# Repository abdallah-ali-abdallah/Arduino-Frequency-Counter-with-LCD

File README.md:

Arduino-Frequency-Counter-with-LCD
==================================

Arduino Frequency Counter with LCD, Everything is Embedded in a single Layer PCB
with maximum frequency input up-to 64 Mhz

  Arduino Frequency Counter (up to 64 Mhz) with LCD
  
  By: Abdallah Ali Abdallah
  
  Date: Aug-2014
  
  Licence: CC-BY-NC V.4
  
  E-mail: abdallah.ali.abdallah.elmasry@gmail.com

  Note: This counter is based on chip 74xx93 (counter) used as a frequency divider by 8
  the maximum bandwidth for arduino to count is 8 Mhz and we can multiply this number 
  using 74xx93 or any other counter chip.

  the new bandwidth is determined by the counter maximum clock rate
  for example: 

  chip 74-LS-93 has (Max clock = 42 Mhz) - so you can measure up to 42 Mhz
  
  chip 74-HC-93 has (Max clock = 64 Mhz) - so you can measure up to 64 Mhz
  
  Note: Minmum input voltage is 2 volt
		    Maximum input voltage is 5.1 volt
		
=============================================	

  This project Based on counter Library by:  
  
  Martin Nawrath KHM LAB3
  Kunsthochschule f¸r Medien Kˆln
  Academy of Media Arts
  http://www.khm.de
  http://interface.khm.de/index.php/labor/experimente/

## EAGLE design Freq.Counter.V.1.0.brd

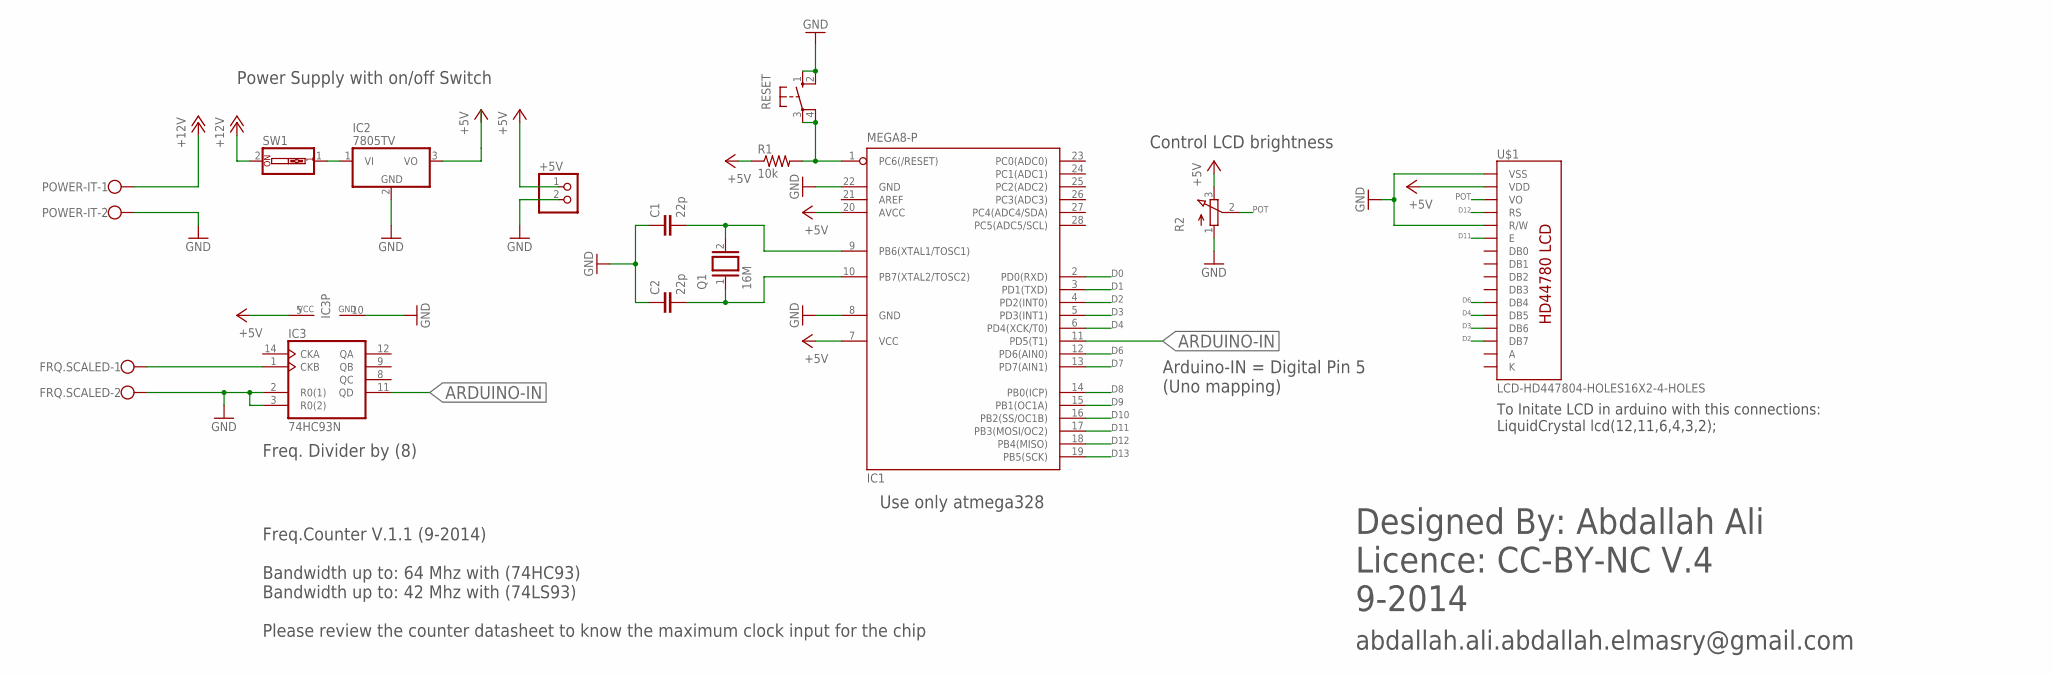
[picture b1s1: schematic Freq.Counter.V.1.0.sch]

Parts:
+5V: PINHD-1X2; 1X02
C1, C2: 22p; C025-025X050
FRQ.SCALED: W237-102
IC1: MEGA8-P; DIL28-3
IC2: 7805TV; TO220V
IC3: 74HC93N; DIL14
POWER-IT: W237-102
Q1: 16M; QS
R1: 10k; 0207/10
R2: 3RP/1610N
RESET: 10-XX; B3F-10XX
SW1: SW_DIP-1; EDG-01
U$1: LCD-HD447804-HOLES16X2-4-HOLES; LCD-16X2-4HOLES

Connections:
+5V: +5V.1, IC1.7 (VCC), IC1.20 (AVCC), IC2.3 (VO), IC3.5 (VCC), R1.1, R2.3 (E), U$1.2 (VDD)
+12V: POWER-IT.1, SW1.2
A: U$1.15 (A)
ARDUINO-IN: IC1.11 (PD5(T1)), IC3.11 (QD)
D0: IC1.2 (PD0(RXD))
D1: IC1.3 (PD1(TXD))
D2: IC1.4 (PD2(INT0)), U$1.14 (DB7)
D3: IC1.5 (PD3(INT1)), U$1.13 (DB6)
D4: IC1.6 (PD4(XCK/T0)), U$1.12 (DB5)
D6: IC1.12 (PD6(AIN0)), U$1.11 (DB4)
D7: IC1.13 (PD7(AIN1))
D8: IC1.14 (PB0(ICP))
D9: IC1.15 (PB1(OC1A))
D10: IC1.16 (PB2(SS/OC1B))
D11: IC1.17 (PB3(MOSI/OC2)), U$1.6 (E)
D12: IC1.18 (PB4(MISO)), U$1.4 (RS)
D13: IC1.19 (PB5(SCK))
GND: +5V.2, C1.1, C2.1, FRQ.SCALED.2, IC1.8 (GND), IC1.22 (GND), IC2.2 (GND), IC3.2 (R0(1)), IC3.3 (R0(2)), IC3.10 (GND), POWER-IT.2, R2.1 (A), RESET.1 (S), RESET.2 (S1), U$1.1 (VSS), U$1.5 (R/W)
K: U$1.16 (K)
unnamed: IC1.1 (PC6(/RESET)), R1.2, RESET.3, RESET.4 (P1)
unnamed: IC2.1 (VI), SW1.1
unnamed: FRQ.SCALED.1, IC3.1 (CKB)
unnamed: C1.2, IC1.9 (PB6(XTAL1/TOSC1)), Q1.2
unnamed: C2.2, IC1.10 (PB7(XTAL2/TOSC2)), Q1.1
POT: R2.2 (S), U$1.3 (VO)

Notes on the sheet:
To Initate LCD in arduino with this connections: LiquidCrystal lcd(12,11,6,4,3,2);
Freq.Counter V.1.1 (9-2014) Bandwidth up to: 64 Mhz with (74HC93) Bandwidth up to: 42 Mhz with (74LS93) Please review the counter datasheet to know the maximum clock input for the chip
Use only atmega328
Power Supply with on/off Switch
Freq. Divider by (8)
Arduino-IN = Digital Pin 5 (Uno mapping)
Control LCD brightness
Designed By: Abdallah Ali Licence: CC-BY-NC V.4 9-2014
abdallah.ali.abdallah.elmasry@gmail.com

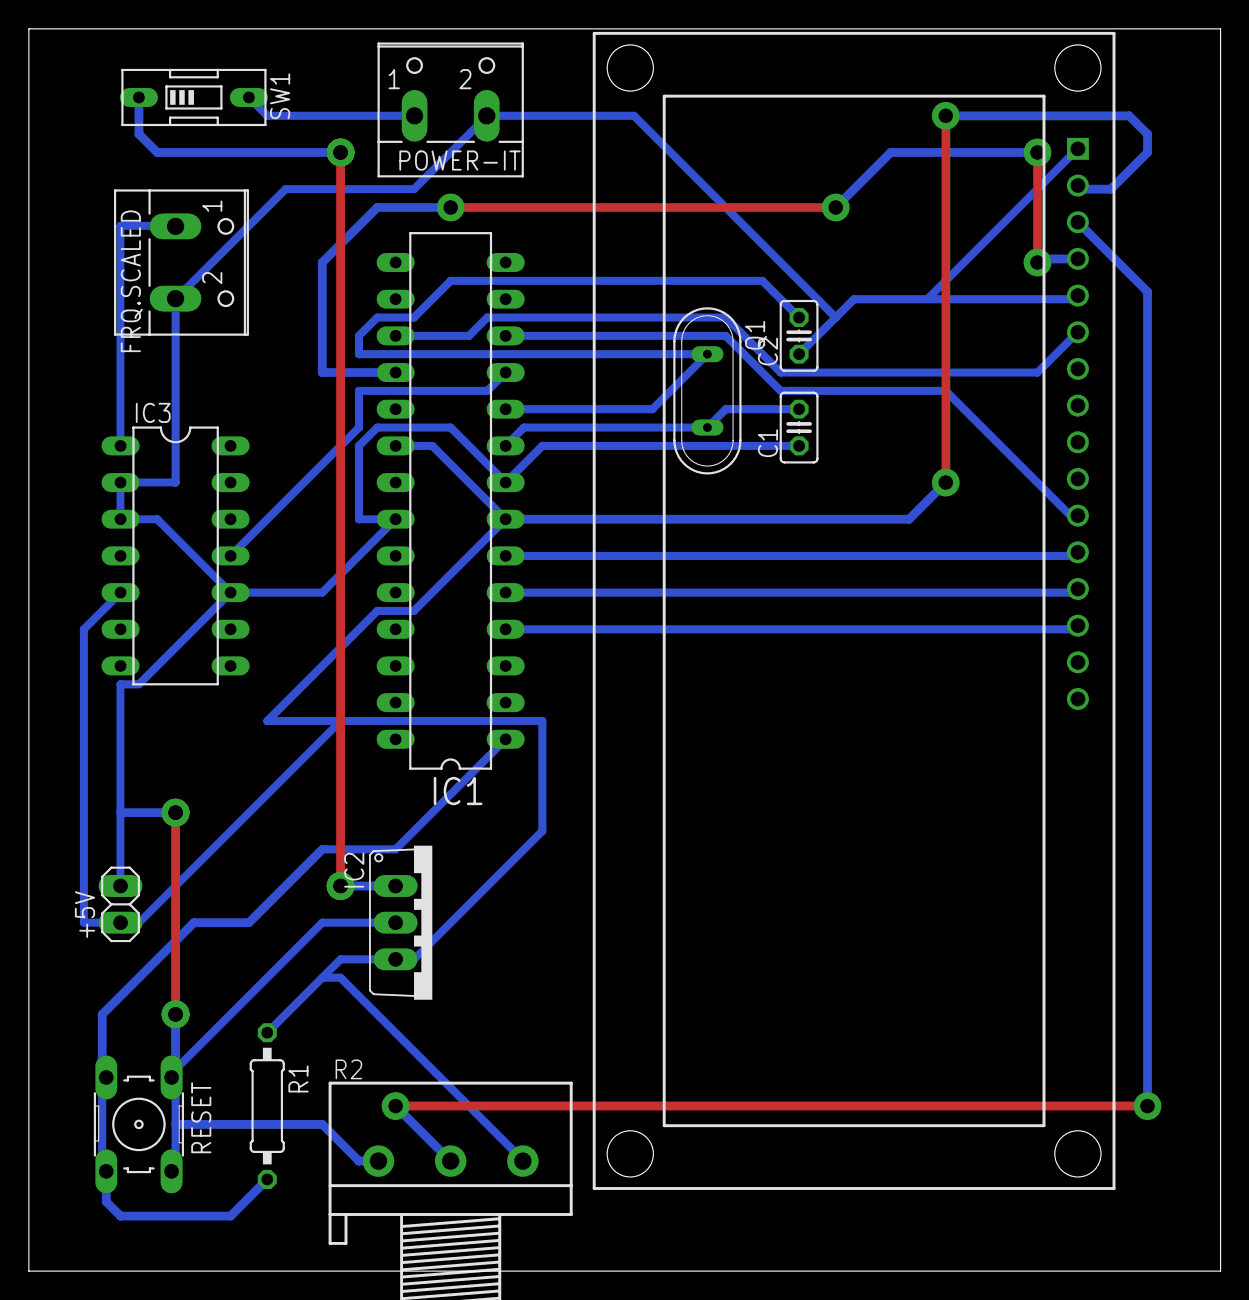
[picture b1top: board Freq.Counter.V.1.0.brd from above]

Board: 2 copper layers, 82.5 x 86.0 mm, 14 parts (0 on the bottom side), 16 nets.

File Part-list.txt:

Partlist

Exported from Freq.Counter.V.1.0.sch at 13/09/2014 08:43:06 ã

EAGLE Version 6.3.0 Copyright (c) 1988-2012 CadSoft

Assembly variant: 

Part       Value                          Device                         Package         Library                      Sheet

+5V                                       PINHD-1X2                      1X02            pinhead                      1
C1         22p                            C-EU025-025X050                C025-025X050    rcl                          1
C2         22p                            C-EU025-025X050                C025-025X050    rcl                          1
FRQ.SCALED                                W237-102                       W237-102        con-wago-500                 1
IC1        MEGA8-P                        MEGA8-P                        DIL28-3         atmel                        1
IC2        7805TV                         7805TV                         TO220V          linear                       1
IC3        74HC93N                        74HC93N                        DIL14           74xx-eu                      1
POWER-IT                                  W237-102                       W237-102        con-wago-500                 1
Q1         16M                            XTAL/S                         QS              special                      1
R1         10k                            R-US_0207/10                   0207/10         rcl                          1
R2                                        3RP/1610N                      3RP/1610N       pot                          1
RESET                                     10-XX                          B3F-10XX        switch-omron                 1
SW1                                       SW_DIP-1                       EDG-01          special                      1
U$1        LCD-HD447804-HOLES16X2-4-HOLES LCD-HD447804-HOLES16X2-4-HOLES LCD-16X2-4HOLES LCD-Library-EagleCAD-HD44780 1

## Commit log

2014-08-29 test a file
2014-08-29 Sketch to use the counter with the PCB+LCD
2014-08-29 Sketch to use the counter with Serial Monitor for tests only
2014-08-29 The PCB File as PDF
2014-08-29 The PCB File as EagleCAD Source
2014-08-29 The Schematics File as EagleCAD Source
2014-08-29 The Schematics File, PDF Version
2014-08-29 LCD library for EagleCAD (16x2 lcd)
2014-08-29 Part List used in this Project
2014-08-29 Schematics, PNG version
2014-08-29 How to build the device
2014-08-29 Top View of the PCB
2014-09-14 Arduino Freq. Counter (up to 64 Mhz) V.1.1
    Arduino Freq. Counter (up to 64 Mhz) V.1.1
    With smaller PCB
